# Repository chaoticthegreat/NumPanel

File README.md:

# NumPad

Assembled Picture (without keys installed and screen)

Schematic

PCB

Case Parts:
Base: 
Top Panel: 

Assembled via screws. 

## Inspiration
I wanted to create a macropad that allowed me to input things into the calculator quickly with layers, sicne my current keyboard does not have a numpad. 

## Challenges
This was my first time using KiCad and Fusion so I had to learn how to use both of those tools. The PCB wiring in KiCad was kinda hard since it was my first time and I made a lot of mistakes. Assembling the case together in fusion was also hard since I had to learn about how mates work. 

## Specifications
BOM: 
- 8x Cherry MX Switches
- 12x SK6812 MINI Leds
- 0.91" OLED screen
- 1x XIA0 RP2040
- 8x Blank DSA Keycaps
- 4x M3x16 Bolt
- 4x M3 Heatset
The macroboard is run using KMK firmware.

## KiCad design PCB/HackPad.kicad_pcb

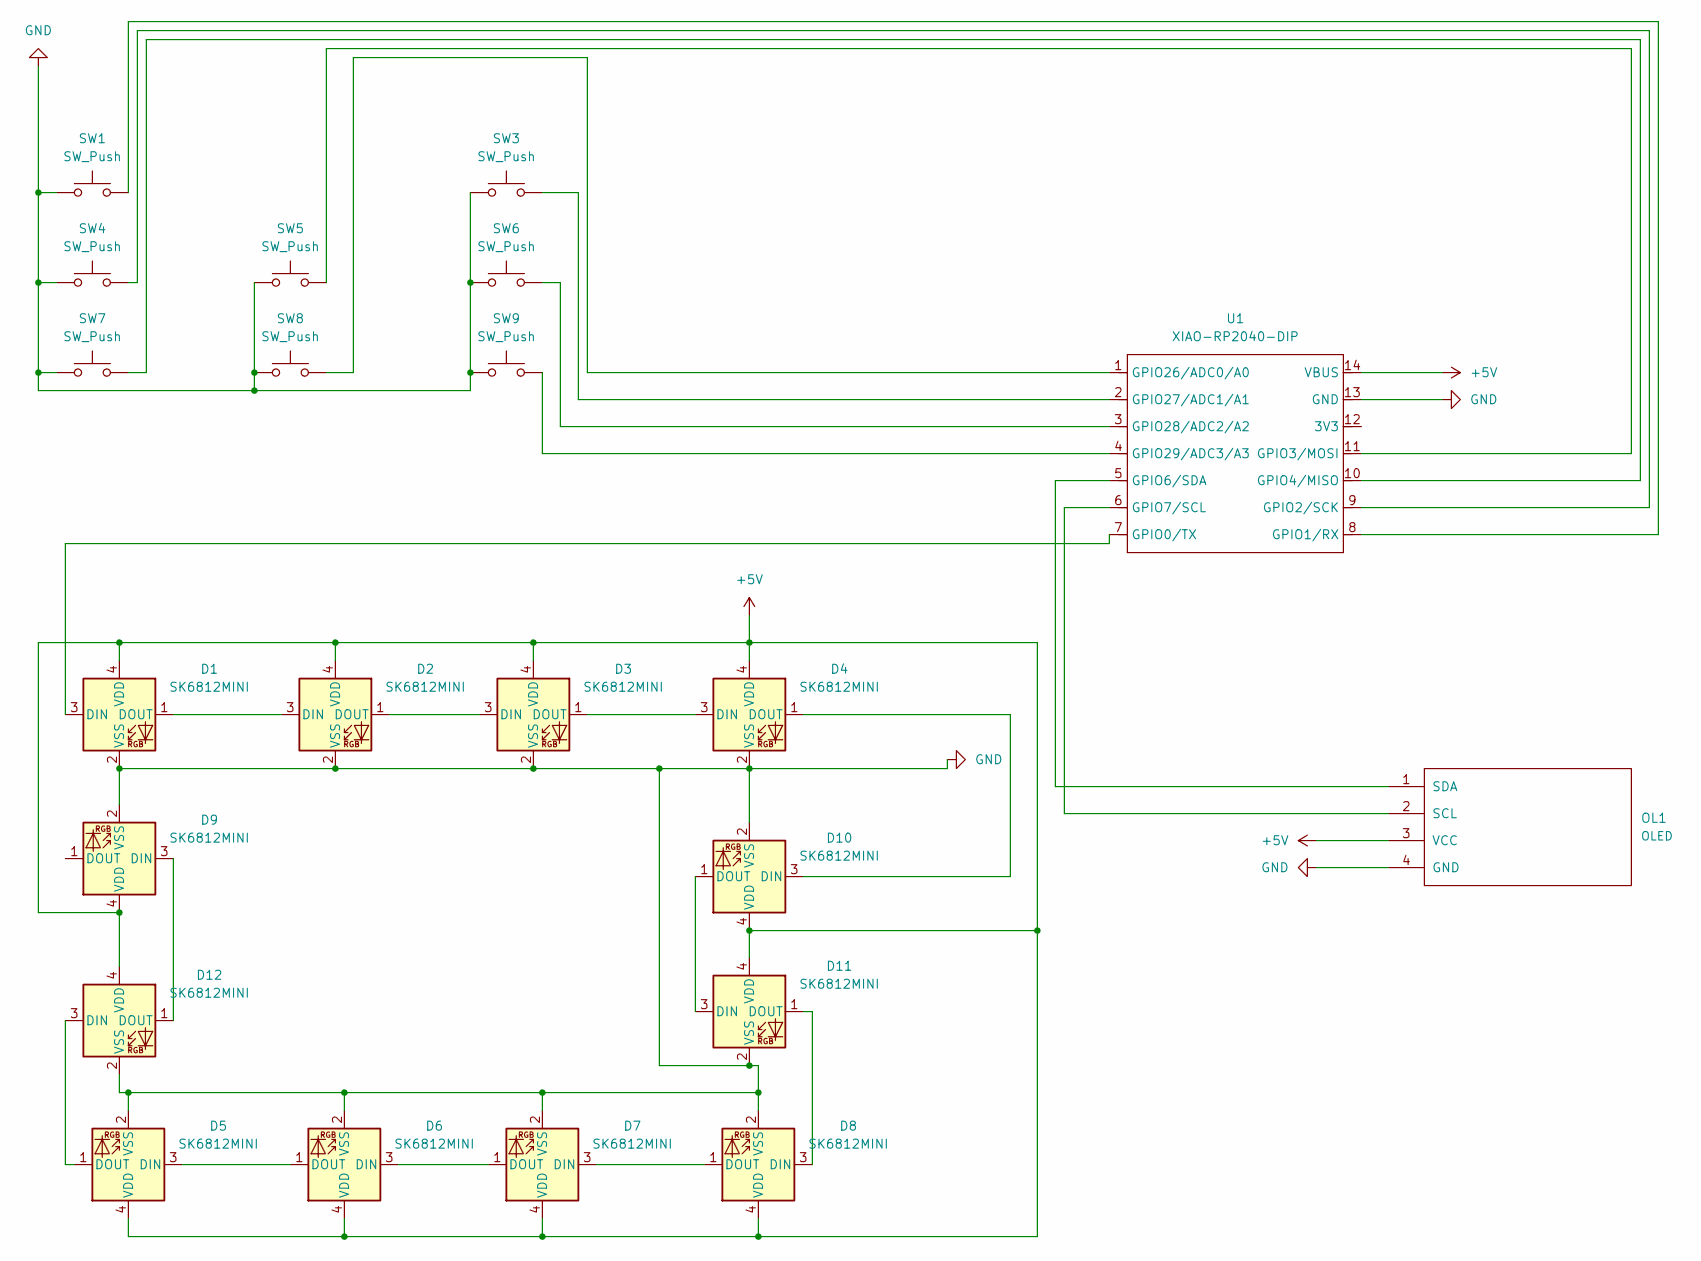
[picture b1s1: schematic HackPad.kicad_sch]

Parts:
D1, D2, D3, D4, D5, D6, D7, D8, D9, D10, D11, D12: SK6812MINI; LED_SK6812MINI_PLCC4_3.5x3.5mm_P1.75mm
OL1: OLED; SSD1306-0.91-OLED-4pin-128x32
SW1, SW3, SW4, SW5, SW6, SW7, SW8, SW9: SW_Push; SW_Cherry_MX_1.00u_PCB
U1: XIAO-RP2040-DIP

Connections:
+5V: D1.4 (VDD), D2.4 (VDD), D3.4 (VDD), D4.4 (VDD), D5.4 (VDD), D6.4 (VDD), D7.4 (VDD), D8.4 (VDD), D9.4 (VDD), D10.4 (VDD), D11.4 (VDD), D12.4 (VDD), OL1.3 (VCC), U1.14 (VBUS)
GND: D1.2 (VSS), D2.2 (VSS), D3.2 (VSS), D4.2 (VSS), D5.2 (VSS), D6.2 (VSS), D7.2 (VSS), D8.2 (VSS), D9.2 (VSS), D10.2 (VSS), D11.2 (VSS), D12.2 (VSS), OL1.4 (GND), SW1.1, SW3.1, SW4.1, SW5.1, SW6.1, SW7.1, SW8.1, SW9.1, U1.13 (GND)
unnamed: D1.3 (DIN), U1.7 (GPIO0/TX)
unnamed: D1.1 (DOUT), D2.3 (DIN)
unnamed: D2.1 (DOUT), D3.3 (DIN)
unnamed: D3.1 (DOUT), D4.3 (DIN)
unnamed: D5.3 (DIN), D6.1 (DOUT)
unnamed: D6.3 (DIN), D7.1 (DOUT)
unnamed: D7.3 (DIN), D8.1 (DOUT)
unnamed: D4.1 (DOUT), D10.3 (DIN)
unnamed: D10.1 (DOUT), D11.3 (DIN)
unnamed: D8.3 (DIN), D11.1 (DOUT)
unnamed: D5.1 (DOUT), D12.3 (DIN)
unnamed: D9.3 (DIN), D12.1 (DOUT)
unnamed: OL1.2 (SCL), U1.6 (GPIO7/SCL)
unnamed: OL1.1 (SDA), U1.5 (GPIO6/SDA)
unnamed: SW1.2, U1.8 (GPIO1/RX)
unnamed: SW4.2, U1.9 (GPIO2/SCK)
unnamed: SW5.2, U1.11 (GPIO3/MOSI)
unnamed: SW7.2, U1.10 (GPIO4/MISO)
unnamed: SW8.2, U1.1 (GPIO26/ADC0/A0)
unnamed: SW3.2, U1.2 (GPIO27/ADC1/A1)
unnamed: SW6.2, U1.3 (GPIO28/ADC2/A2)
unnamed: SW9.2, U1.4 (GPIO29/ADC3/A3)

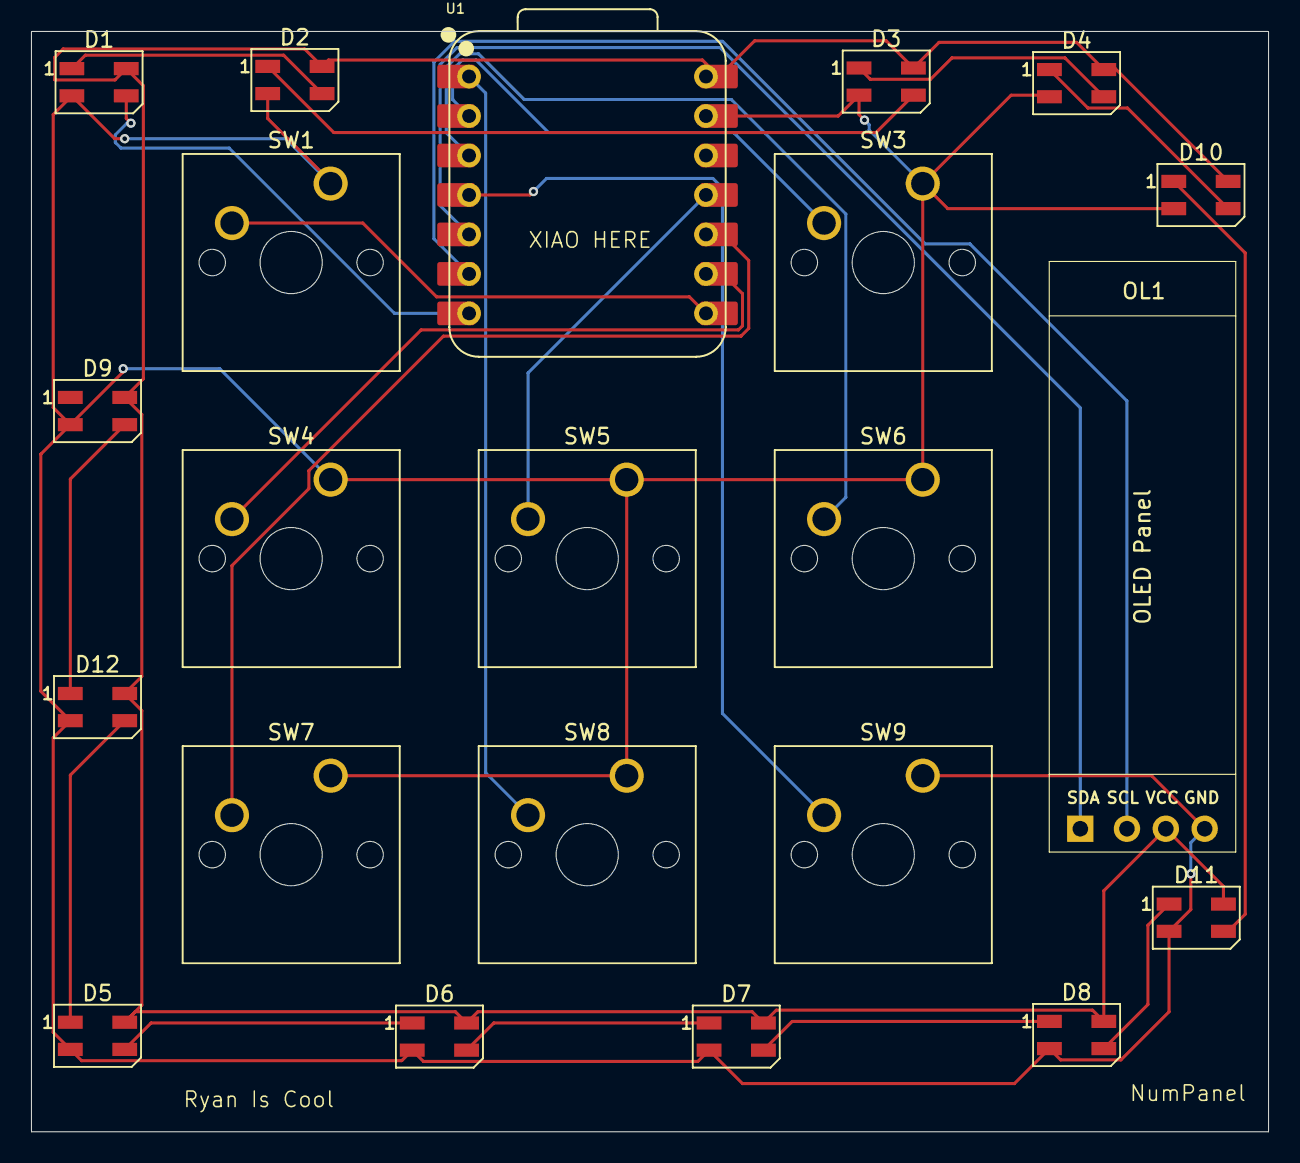
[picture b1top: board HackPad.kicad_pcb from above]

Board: 2 copper layers, 79.6 x 70.8 mm, 22 parts (0 on the bottom side), 24 nets.

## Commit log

2025-07-02 firmware
2025-07-02 move firmware
2025-07-04 change assembly file format
